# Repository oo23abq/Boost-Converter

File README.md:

# Boost-Converter-PCB
simple design of a boost converter PCB in kicad

## Repository Structure

```markdown

```text
├── docs/                               # General Documentation  
│   └── testreport.txt                  # Lab Test Report  
├── kicad/                              # KiCAD Project Files 
│   ├── Boost Converter.kicad_pcb       # PCB Board File
│   ├── Boost Converter.kicad_sch       # Schematic File 
│   ├── bom.csv                         # Bill of Materials
│   ├── gerbers/                        # Manufacturing Files 
│   │   └── boost.zip                   # Gerber and NC Drill Archives 
│   └── images/                         # 3D Renders 
│       ├── boostconverter_bottom.png   # Bottom Layer 
│       └── boostconverter_top.png      # Top Layer 
├── ltspice/                            # Analogue Simulation 
│   ├── schematic.asc                   # LTspice Schematic
│   └── waveform.asc                    # Plot pane waveform
├── testing/                            # Lab Testing
│   ├── oscilloscopeinput.png           # Input Voltage Waveform  
│   ├── oscilloscopeoutput.png          # Output Voltage Transient Response
│   └── testsetup.png                   # Bench test setup 
├── LICENSE                             # MIT License File 
└── README.md                           # Project Guidance / Info

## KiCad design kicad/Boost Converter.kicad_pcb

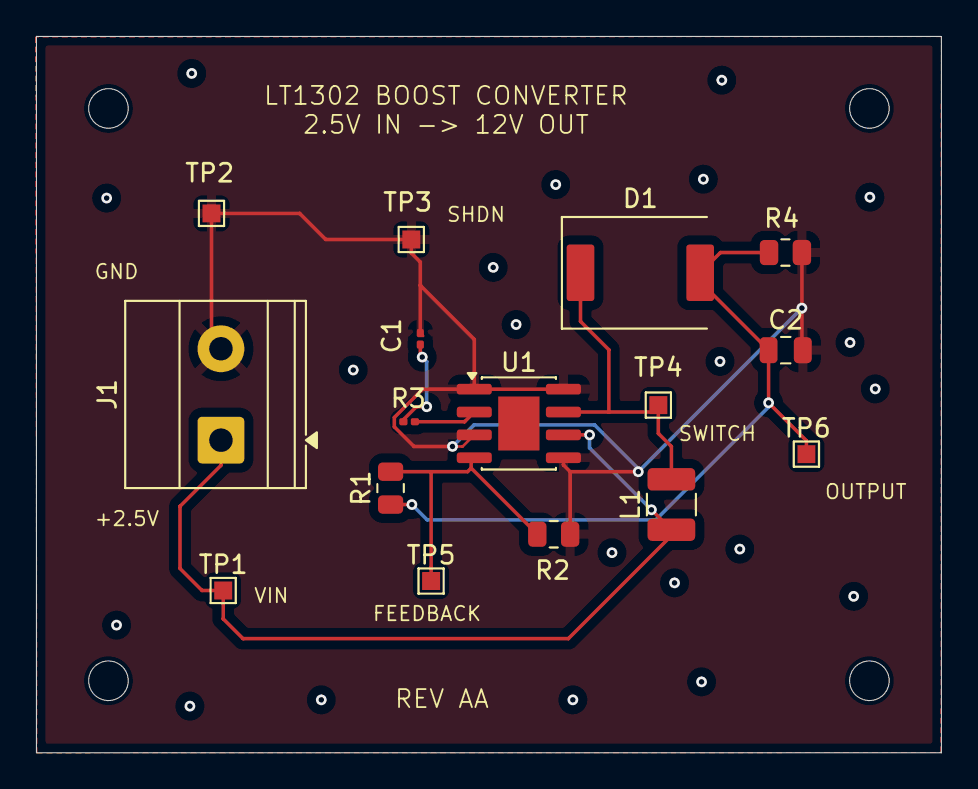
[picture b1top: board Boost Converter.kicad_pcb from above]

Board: 2 copper layers, 50.3 x 39.8 mm, 20 parts (0 on the bottom side), 7 nets.

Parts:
C1: 0.01µ; C_0201_0603Metric
C2: 100µ; C_0805_2012Metric
D1: MBRS340; ST_D_SMC
J1: Conn_01x02_Pin; TerminalBlock_Phoenix_MKDS-1,5-2-5.08_1x02_P5.08mm_Horizont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
L1: 3.3µ; L_1210_3225Metric
MH1, MH2, MH3, MH4: MountingHole_2.2mm_M2
R1: 86.6k; R_0805_2012Metric
R2: 10k; R_0805_2012Metric
R3: 20K; R_0201_0603Metric
R4: 240; R_0805_2012Metric
TP1, TP2, TP3, TP4, TP5, TP6: TestPoint; TestPoint_Pad_1.0x1.0mm
U1: LT1302; SOIC-8-1EP_3.9x4.9mm_P1.27mm_EP2.29x3mm

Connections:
FB: R1.2, R2.1, TP5.1, U1.4 (FB)
GND: C1.2, C2.2 (B), J1.2, R2.2, R4.2, TP2.1, TP3.1, U1.1 (GND), U1.3 (SHDN), U1.5 (It), U1.8 (PGND)
IN: J1.1, L1.1, TP1.1, U1.6 (Vin)
unnamed: R3.1, U1.2 (Vc)
OUT: C2.1 (A), D1.2 (-), R1.1, R4.1, TP6.1
Vc: C1.1, R3.2
Vsw: D1.1 (+), L1.2, TP4.1, U1.7 (SW)
